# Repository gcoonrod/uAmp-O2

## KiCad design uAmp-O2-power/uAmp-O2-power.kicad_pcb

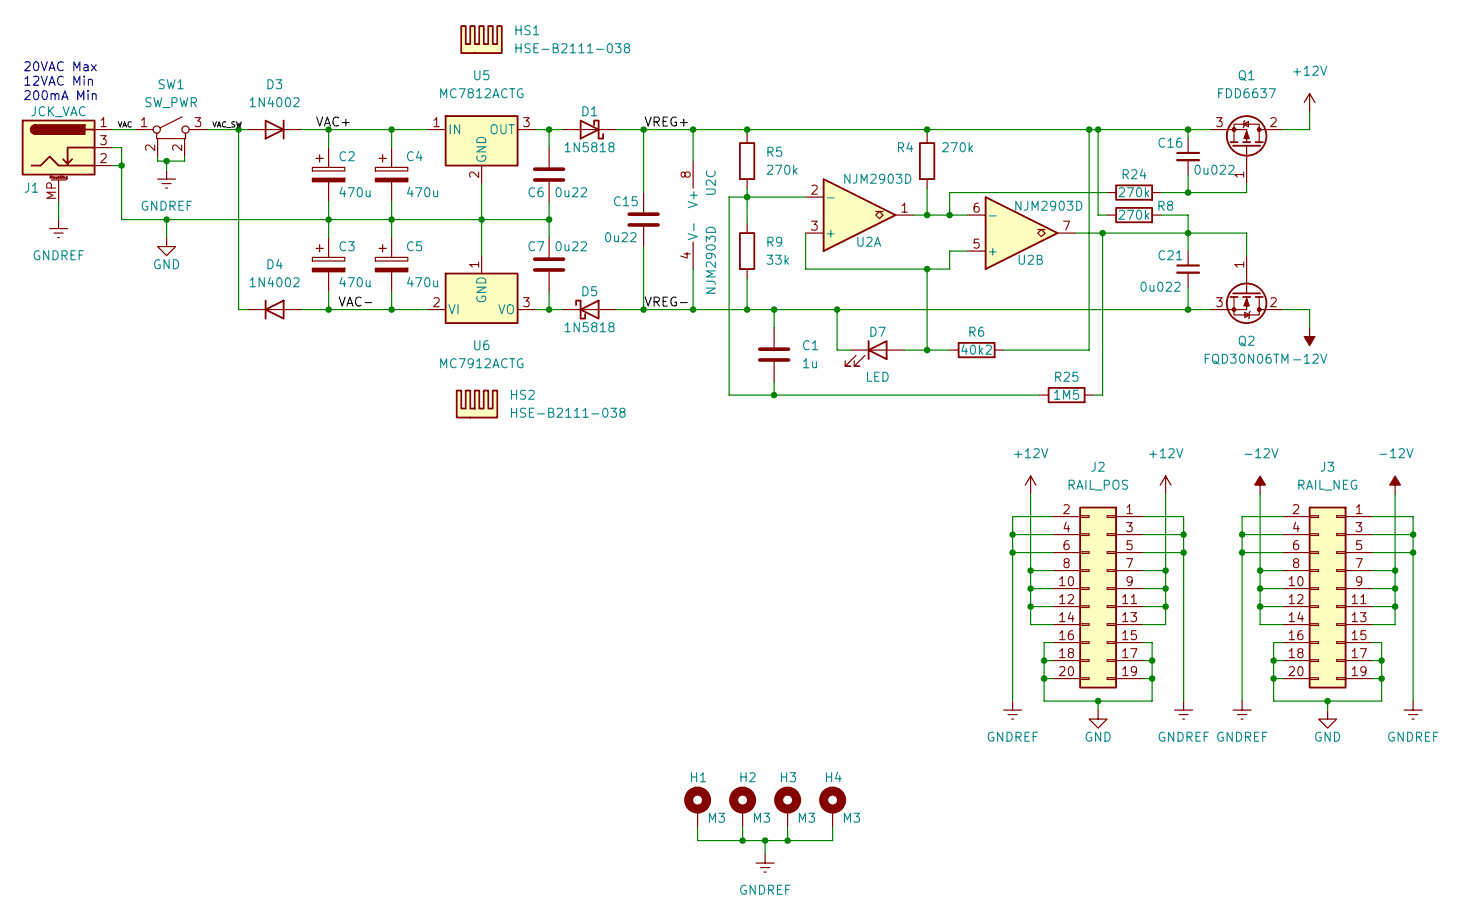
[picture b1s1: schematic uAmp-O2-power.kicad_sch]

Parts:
C1: 1u; C_Disc_D5.0mm_W2.5mm_P2.50mm; Manufacturer Part Number K105Z20Y5VF5TL2
C2, C3, C4, C5: 470u; CP_Radial_D12.5mm_P5.00mm; Manufacturer Part Number EKY-350ELL471MK15S
C6, C7, C15: 0u22; C_Rect_L7.2mm_W2.5mm_P5.00mm_FKS2_FKP2_MKS2_MKP2; Manufacturer Part Number B32529C0224K289
C16, C21: 0u022; C_Disc_D5.0mm_W2.5mm_P5.00mm; Manufacturer Part Number FK28X7R1H223KN000
D1, D5: 1N5818; D_DO-41_SOD81_P3.81mm_Vertical_AnodeUp; Manufacturer Part Number 1N5818
D3, D4: 1N4002; D_DO-41_SOD81_P3.81mm_Vertical_AnodeUp; Manufacturer Part Number 1N4007-TP
D7: LED; LED_Dialight_551; Manufacturer Part Number 5510407F
H1, H2, H3, H4: M3; MountingHole_3.2mm_M3_Pad_Via
HS1, HS2: HSE-B2111-038; Heatsink_CUI_HSE-B2111-038; Manufacturer Part Number HSE-B2111-038
J1: JCK_VAC; Connector_BarrelJack_Switchcraft_RAPC712S; Manufacturer Part Number RAPC712S
J2: RAIL_POS; PinSocket_2x10_P2.54mm_Vertical
J3: RAIL_NEG; PinSocket_2x10_P2.54mm_Vertical
Q1: FDD6637; TO-252-2; Manufacturer Part Number FDD6637
Q2: FQD30N06TM; TO-252-2; Manufacturer Part Number FQD30N06TM
R4, R5, R8, R24: 270k; R_Axial_DIN0207_L6.3mm_D2.5mm_P10.16mm_Horizontal; Manufacturer Part Number HVR2500002703FR500
R6: 40k2; R_Axial_DIN0204_L3.6mm_D1.6mm_P7.62mm_Horizontal; Manufacturer Part Number SFR16S0004022FR500
R9: 33k; R_Axial_DIN0207_L6.3mm_D2.5mm_P10.16mm_Horizontal; Manufacturer Part Number MFP-25BRD52-33K
R25: 1M5; R_Axial_DIN0207_L6.3mm_D2.5mm_P10.16mm_Horizontal; Manufacturer Part Number RNV14FAL1M50
SW1: SW_PWR; Switch_SPST_eSwitch_800A-WSP9-M6; Manufacturer Part Number 800AWSP9M6QE
U2: NJM2903D; DIP-8_W7.62mm_Socket_LongPads; Manufacturer Part Number NJM2903D
U5: MC7812ACTG; TO-220-3_Vertical; Manufacturer Part Number MC7812ACTG
U6: MC7912ACTG; TO-220-3_Vertical; Manufacturer Part Number MC7912ACTG

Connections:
+12V: J2.7, J2.8, J2.9, J2.10, J2.11, J2.12, J2.13, J2.14, Q1.2 (D)
-12V: J3.7, J3.8, J3.9, J3.10, J3.11, J3.12, J3.13, J3.14, Q2.2 (D)
/VAC: J1.1, SW1.1 (A)
/VAC+: C2.1, C4.1, D3.1 (K), U5.1 (IN)
/VAC-: C3.2, C5.2, D4.2 (A), U6.2 (VI)
/VAC_SW: D3.2 (A), D4.1 (K), SW1.3 (B)
/VREG+: C15.1, C16.1, D1.1 (K), Q1.3 (S), R4.1, R5.1, R6.2, R8.1, U2.8 (V+)
/VREG-: C1.1, C15.2, C21.2, D5.2 (A), D7.1 (K), Q2.3 (S), R9.2, U2.4 (V-)
GND: C2.2, C3.1, C4.2, C5.1, C6.2, C7.1, J1.2, J1.3, J2.15, J2.16, J2.17, J2.18, J2.19, J2.20, J3.15, J3.16, J3.17, J3.18, J3.19, J3.20, U5.2 (GND), U6.1 (GND)
GNDREF: H1.1, H2.1, H3.1, H4.1, J1.MP (MountPin), J2.1, J2.2, J2.3, J2.4, J2.5, J2.6, J3.1, J3.2, J3.3, J3.4, J3.5, J3.6, SW1.2 (MP)
unnamed: C16.2, Q1.1 (G), R24.2
unnamed: R4.2, R24.1, U2.1, U2.6 (-)
unnamed: C1.2, R5.2, R9.1, R25.1, U2.2 (-)
unnamed: D7.2 (A), R6.1, U2.3 (+), U2.5 (+)
unnamed: C21.1, Q2.1 (G), R8.2, R25.2, U2.7
unnamed: C6.1, D1.2 (A), U5.3 (OUT)
unnamed: C7.2, D5.1 (K), U6.3 (VO)

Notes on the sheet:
20VAC Max 12VAC Min 200mA Min

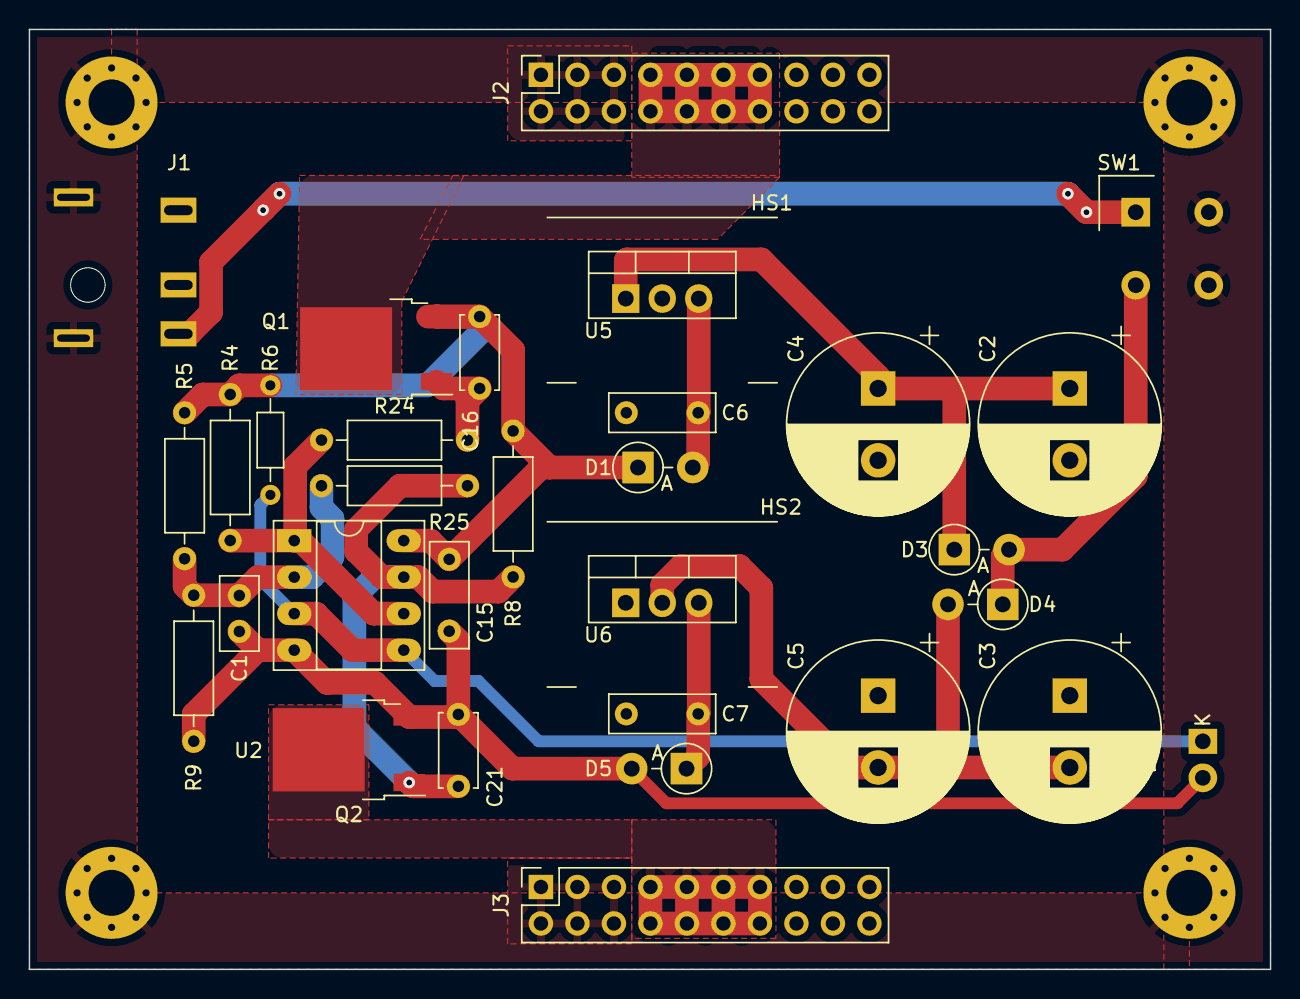
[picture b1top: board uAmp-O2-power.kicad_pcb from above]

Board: 2 copper layers, 86.4 x 65.4 mm, 37 parts (0 on the bottom side), 17 nets.

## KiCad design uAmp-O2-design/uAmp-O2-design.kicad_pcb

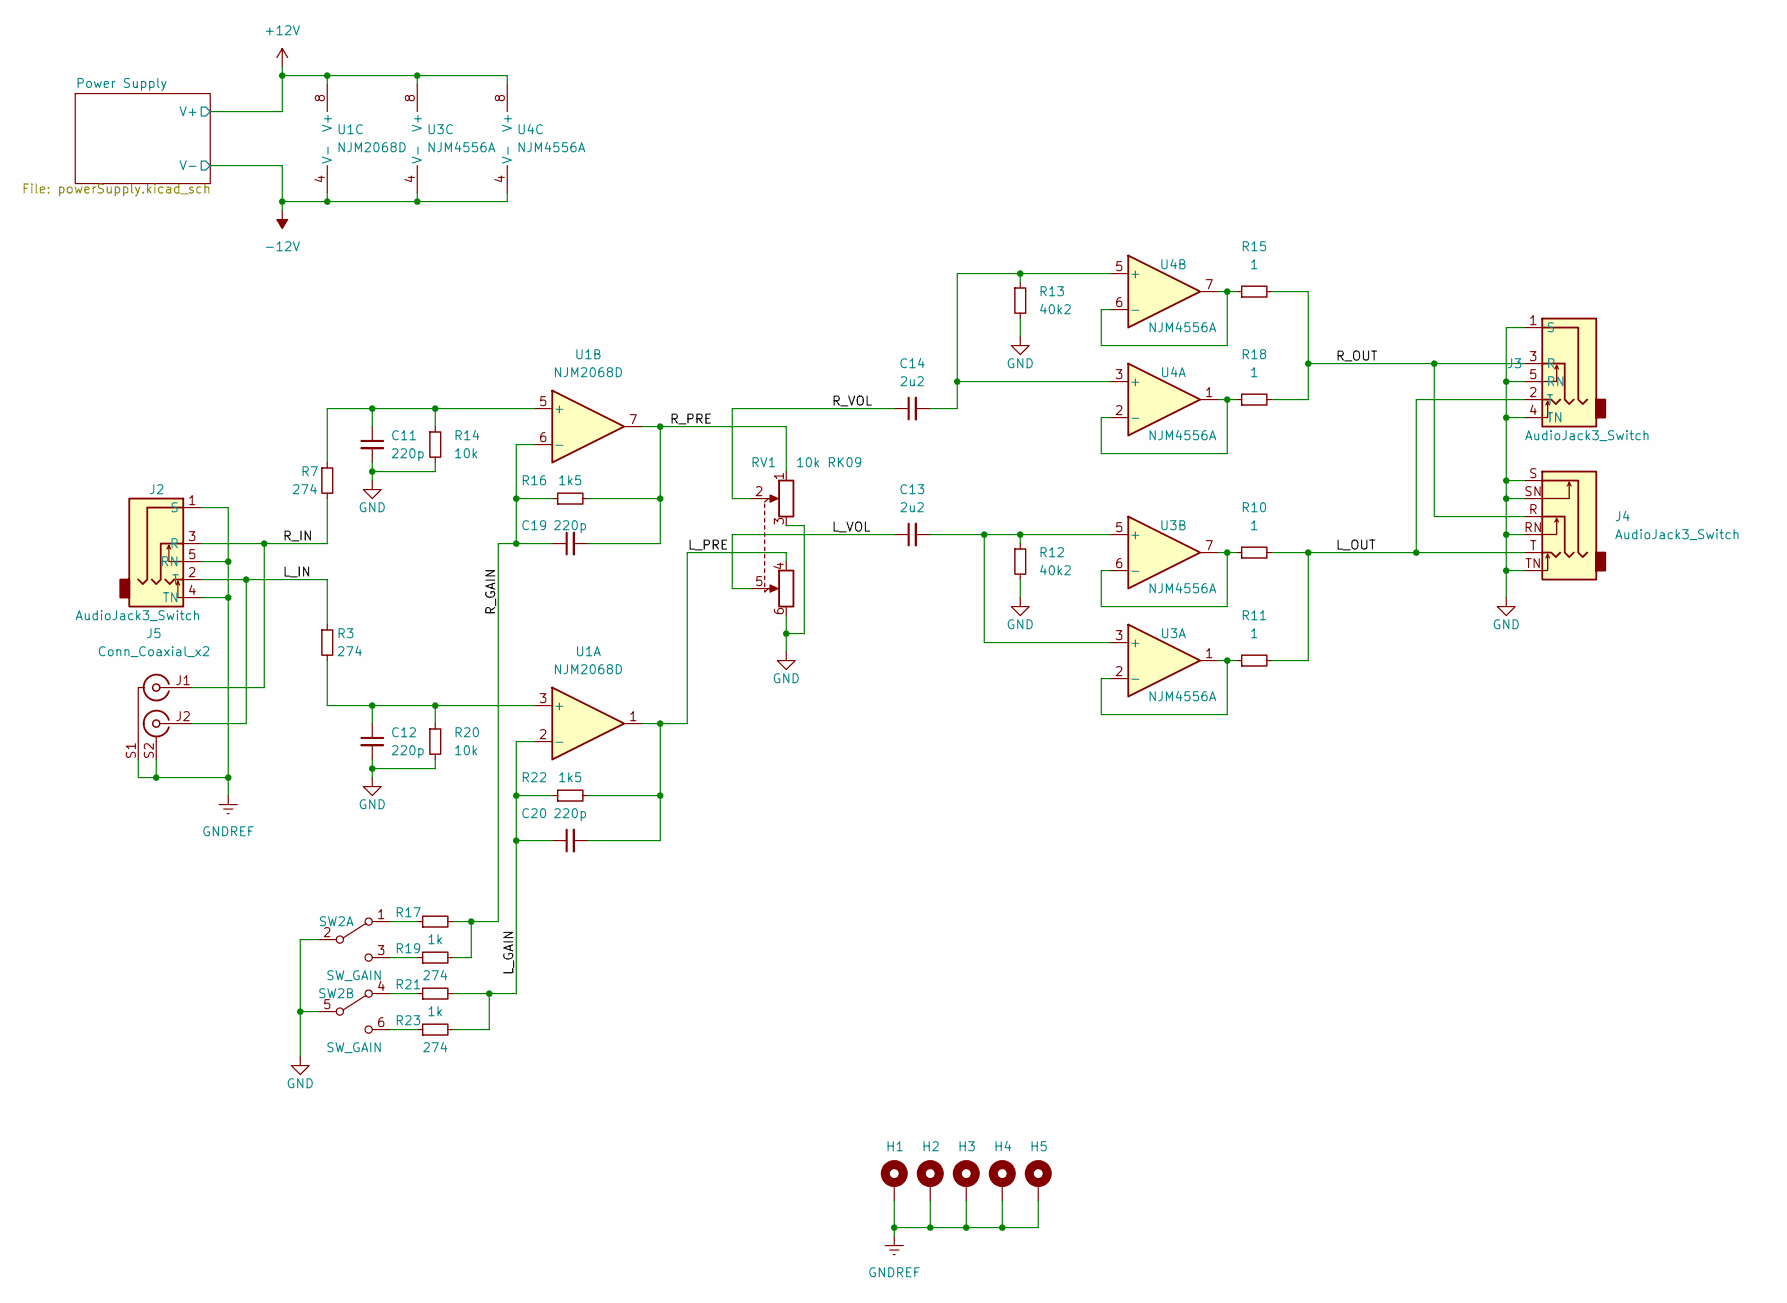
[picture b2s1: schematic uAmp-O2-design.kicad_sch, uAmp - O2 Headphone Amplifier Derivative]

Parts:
C11, C12, C19, C20: 220p; C_Disc_D5.0mm_W2.5mm_P2.50mm; Manufacturer Part Number K221J15C0GH5TL2
C13, C14: 2u2; C_Rect_L7.2mm_W7.2mm_P5.00mm_FKS2_FKP2_MKS2_MKP2; Manufacturer Part Number MMK5225K63J06L4BULK
H1, H2, H3, H4, H5: M2; MountingHole_3.2mm_M3_Pad
J2, J3: AudioJack3_Switch; Connector_AudioJack_1.8mmTRS_SJ13535NS; Manufacturer Part Number SJ1-3535NS
J4: AudioJack3_Switch; Connector_AudioJack_3.5mmTRS_IO-TJ6HH; Manufacturer Part Number IO-TJ6HH
J5: Conn_Coaxial_x2; PJRAS2X1S01AUX; Manufacturer Part Number PJRAS2X1S01AUX
R3, R7, R19, R23: 274; R_Axial_DIN0204_L3.6mm_D1.6mm_P7.62mm_Horizontal; Manufacturer Part Number SFR16S0002740FR500
R10, R11, R15, R18: 1; R_Axial_DIN0207_L6.3mm_D2.5mm_P10.16mm_Horizontal; Manufacturer Part Number MFR50SFTE52-1R
R12, R13: 40k2; R_Axial_DIN0204_L3.6mm_D1.6mm_P7.62mm_Horizontal; Manufacturer Part Number SFR16S0004022FR500
R14, R20: 10k; R_Axial_DIN0204_L3.6mm_D1.6mm_P7.62mm_Horizontal; Manufacturer Part Number RN50C1002FRE6
R16, R22: 1k5; R_Axial_DIN0204_L3.6mm_D1.6mm_P7.62mm_Horizontal; Manufacturer Part Number SFR16S0001501FR500
R17, R21: 1k; R_Axial_DIN0204_L3.6mm_D1.6mm_P7.62mm_Horizontal; Manufacturer Part Number MRS16000C1001FRP00
RV1: 10k RK09; Potentiometer_Bourns_PTD902; Manufacturer Part Number PTD902-1025K-A103
SW2: SW_GAIN; Switch_Button_DPDT_C&K_PN22SJNA03QE; Manufacturer Part Number PN22SJNA03QE
U1: NJM2068D; DIP-8_W7.62mm_Socket_LongPads; Manufacturer Part Number NJM2068D
U3, U4: NJM4556A; DIP-8_W7.62mm_Socket_LongPads; Manufacturer Part Number NJM4556AD

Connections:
+12V: U1.8 (V+), U3.8 (V+), U4.8 (V+); also elsewhere on the board
-12V: U1.4 (V-), U3.4 (V-), U4.4 (V-); also elsewhere on the board
/L_GAIN: C20.1, R21.2, R22.1, R23.2, U1.2 (-)
/L_IN: J2.2 (T), J5.J2 (IN2), R3.1
/L_OUT: J3.2 (T), J4.T, R10.2, R11.2
/L_PRE: C20.2, R22.2, RV1.4, U1.1
/L_VOL: C13.1, RV1.5
/R_GAIN: C19.1, R16.1, R17.2, R19.2, U1.6 (-)
/R_IN: J2.3 (R), J5.J1 (IN1), R7.2
/R_OUT: J3.3 (R), J4.R, R15.2, R18.2
/R_PRE: C19.2, R16.2, RV1.1, U1.7
/R_VOL: C14.1, RV1.2
GND: C11.2, C12.2, J3.1 (S), J3.4 (TN), J3.5 (RN), J4.RN, J4.S, J4.SN, J4.TN, R12.2, R13.2, R14.2, R20.2, RV1.3, RV1.6, SW2.2 (B), SW2.5 (B); also elsewhere on the board
unnamed: C11.1, R7.1, R14.1, U1.5 (+)
unnamed: C12.1, R3.2, R20.1, U1.3 (+)
unnamed: C13.2, R12.1, U3.3 (+), U3.5 (+)
unnamed: C14.2, R13.1, U4.3 (+), U4.5 (+)
unnamed: R10.1, U3.6 (-), U3.7
unnamed: R11.1, U3.1, U3.2 (-)
unnamed: R15.1, U4.6 (-), U4.7
unnamed: R17.1, SW2.1 (A)
unnamed: R18.1, U4.1, U4.2 (-)
unnamed: R19.1, SW2.3 (C)
unnamed: R21.1, SW2.4 (A)
unnamed: R23.1, SW2.6 (C)

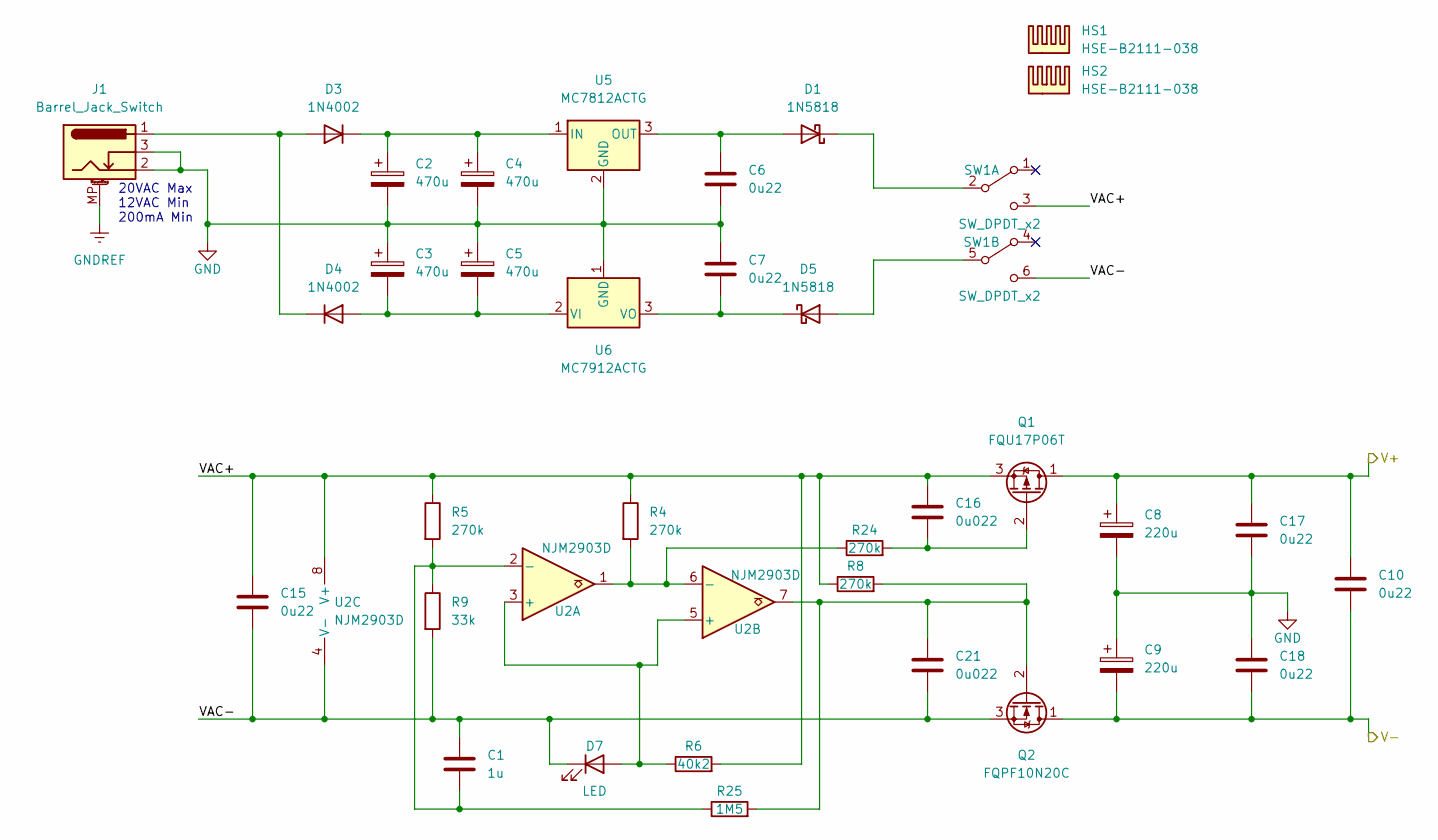
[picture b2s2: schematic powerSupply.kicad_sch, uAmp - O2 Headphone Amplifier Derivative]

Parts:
C1: 1u; C_Disc_D5.0mm_W2.5mm_P2.50mm; Manufacturer Part Number K105Z20Y5VF5TL2
C2, C3, C4, C5: 470u; CP_Radial_D12.5mm_P5.00mm; Manufacturer Part Number EKY-350ELL471MK15S
C6, C7, C10, C15, C17, C18: 0u22; C_Rect_L7.2mm_W2.5mm_P5.00mm_FKS2_FKP2_MKS2_MKP2; Manufacturer Part Number B32529C0224K289
C8, C9: 220u; CP_Radial_D8.0mm_P3.50mm; Manufacturer Part Number UPW1E221MPD
C16, C21: 0u022; C_Disc_D5.0mm_W2.5mm_P5.00mm; Manufacturer Part Number FK28X7R1H223KN000
D1, D5: 1N5818; D_DO-41_SOD81_P3.81mm_Vertical_AnodeUp; Manufacturer Part Number 1N5818
D3, D4: 1N4002; D_DO-41_SOD81_P3.81mm_Vertical_AnodeUp; Manufacturer Part Number 1N4007-TP
D7: LED; LED_Dialight_551; Manufacturer Part Number 5510407F
HS1, HS2: HSE-B2111-038; Heatsink_CUI_HSE-B2111-038; Manufacturer Part Number HSE-B2111-038
J1: Barrel_Jack_Switch; Connector_BarrelJack_Switchcraft_RAPC712S; Manufacturer Part Number RAPC712S
Q1: FQU17P06T; TO-220F-3_Vertical; Manufacturer Part Number FQPF15P12
Q2: FQPF10N20C; TO-220-3_Vertical; Manufacturer Part Number IRFIZ48GPBF
R4, R5, R8, R24: 270k; R_Axial_DIN0207_L6.3mm_D2.5mm_P10.16mm_Horizontal; Manufacturer Part Number HVR2500002703FR500
R6: 40k2; R_Axial_DIN0204_L3.6mm_D1.6mm_P7.62mm_Horizontal; Manufacturer Part Number SFR16S0004022FR500
R9: 33k; R_Axial_DIN0207_L6.3mm_D2.5mm_P10.16mm_Horizontal; Manufacturer Part Number MFP-25BRD52-33K
R25: 1M5; R_Axial_DIN0207_L6.3mm_D2.5mm_P10.16mm_Horizontal; Manufacturer Part Number RNV14FAL1M50
SW1: SW_DPDT_x2; Switch_Button_DPDT_C&K_PN22SJNA03QE; Manufacturer Part Number PN22SJNA03QE
U2: NJM2903D; DIP-8_W7.62mm_Socket_LongPads; Manufacturer Part Number NJM2903D
U5: MC7812ACTG; TO-220-3_Vertical; Manufacturer Part Number MC7812ACTG
U6: MC7912ACTG; TO-220-3_Vertical; Manufacturer Part Number MC7912ACTG

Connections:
+12V: C8.1, C10.1, C17.1, Q1.1 (D); also elsewhere on the board
-12V: C9.2, C10.2, C18.2, Q2.1 (D); also elsewhere on the board
/Power Supply/VAC+: C15.1, C16.1, Q1.3 (S), R4.1, R5.1, R6.2, R8.1, SW1.3 (C), U2.8 (V+)
/Power Supply/VAC-: C1.1, C15.2, C21.2, D7.1 (K), Q2.3 (S), R9.2, SW1.6 (C), U2.4 (V-)
GND: C2.2, C3.1, C4.2, C5.1, C6.2, C7.1, C8.2, C9.1, C17.2, C18.1, J1.2, J1.3, U5.2 (GND), U6.1 (GND); also elsewhere on the board
unnamed: C1.2, R5.2, R9.1, R25.1, U2.2 (-)
unnamed: C2.1, C4.1, D3.1 (K), U5.1 (IN)
unnamed: C3.2, C5.2, D4.2 (A), U6.2 (VI)
unnamed: C6.1, D1.2 (A), U5.3 (OUT)
unnamed: C7.2, D5.1 (K), U6.3 (VO)
unnamed: C16.2, Q1.2 (G), R24.2
unnamed: C21.1, Q2.2 (G), R8.2, R25.2, U2.7
unnamed: D1.1 (K), SW1.2 (B)
unnamed: D3.2 (A), D4.1 (K), J1.1
unnamed: D5.2 (A), SW1.5 (B)
unnamed: D7.2 (A), R6.1, U2.3 (+), U2.5 (+)
unnamed: R4.2, R24.1, U2.1, U2.6 (-)

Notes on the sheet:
20VAC Max 12VAC Min 200mA Min

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
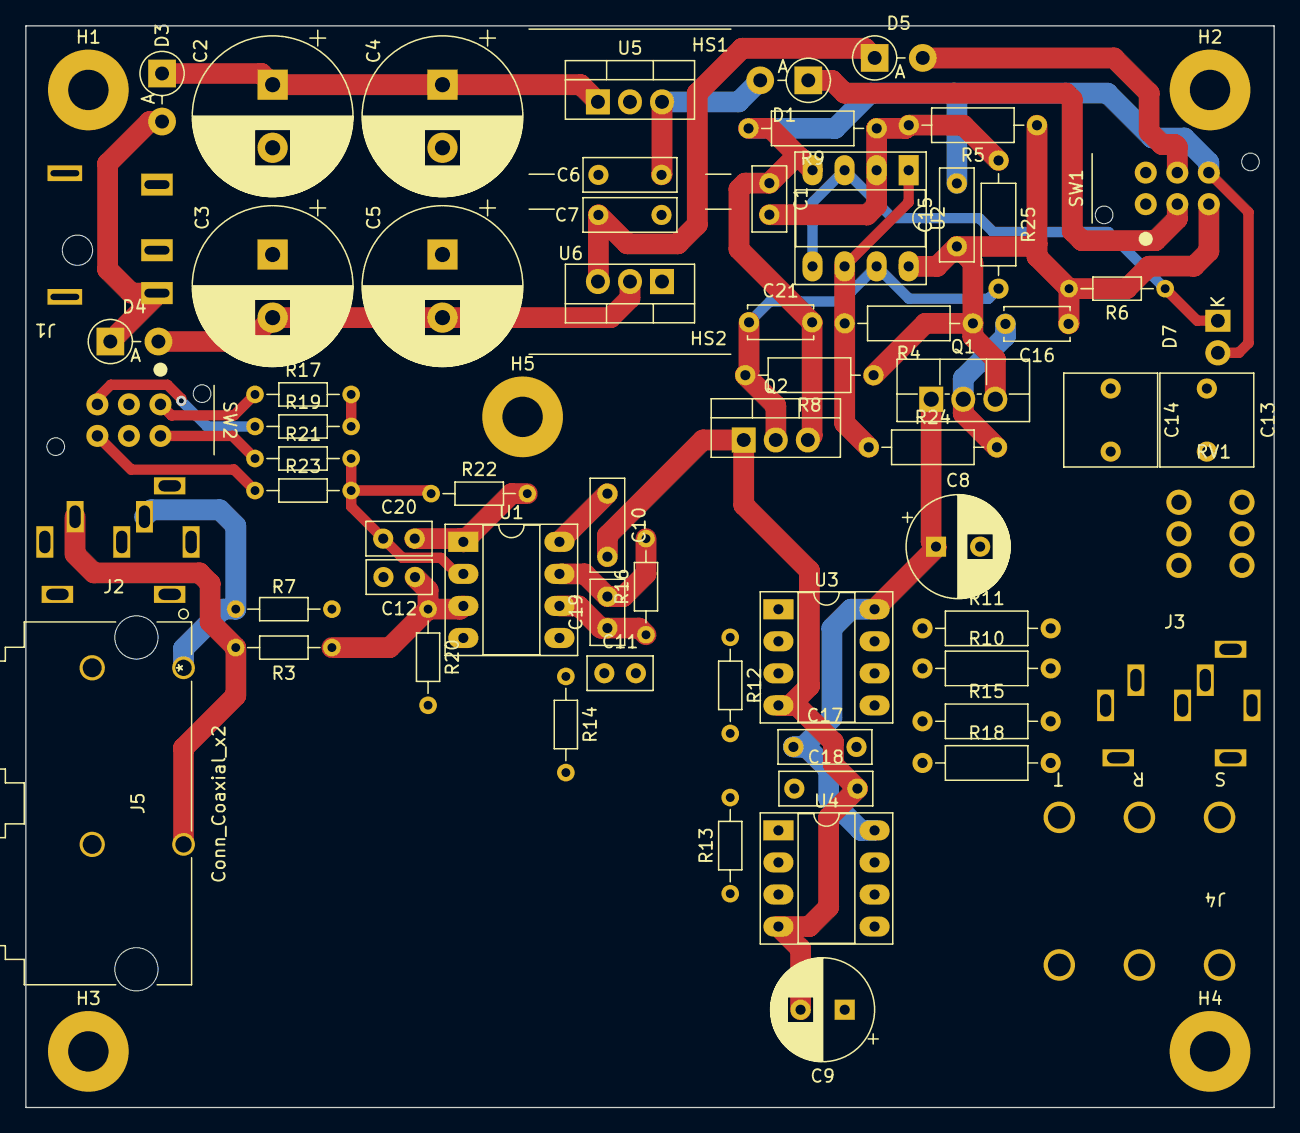
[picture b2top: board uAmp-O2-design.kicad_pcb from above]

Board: 2 copper layers, 98.9 x 85.7 mm, 72 parts (0 on the bottom side), 40 nets.

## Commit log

2023-01-31 Stopping single board version work.
2023-01-31 Split board start. First pass at power board
